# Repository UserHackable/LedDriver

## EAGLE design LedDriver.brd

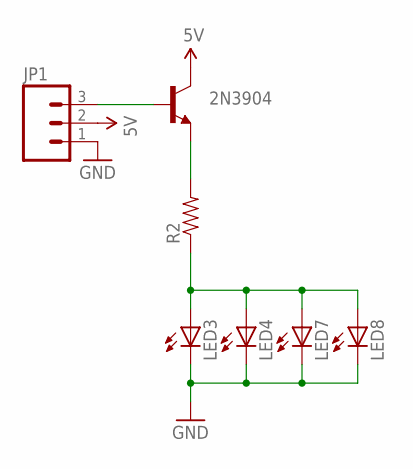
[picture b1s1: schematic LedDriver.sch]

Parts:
2N3904: TRANSISTOR_NPNTO-92-AMMO; TO-92-AMMO
JP1: M03PTH; 1X03
LED3, LED4, LED7, LED8: LED5MM
R2: RESISTORAXIAL-0.3; AXIAL-0.3

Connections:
5V: 2N3904.3 (C), JP1.2
GND: JP1.1, LED3.K (C), LED4.K (C), LED7.K (C), LED8.K (C)
unnamed: LED3.A, LED4.A, LED7.A, LED8.A, R2.P$1 (1)
unnamed: 2N3904.1 (E), R2.P$2 (2)
unnamed: 2N3904.2 (B), JP1.3

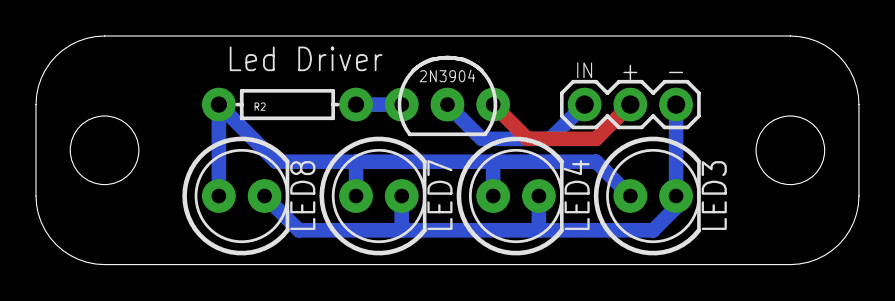
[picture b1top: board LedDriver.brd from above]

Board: 2 copper layers, 45.7 x 12.7 mm, 7 parts (0 on the bottom side), 5 nets.

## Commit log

2016-04-06 updating stuff
2016-04-07 from Makefile

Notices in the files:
parts and their libraries:
SparkFun-Connectors: Licensing: Creative Commons ShareAlike 4.0 International - https://creativecommons.org/licenses/by-sa/4.0
